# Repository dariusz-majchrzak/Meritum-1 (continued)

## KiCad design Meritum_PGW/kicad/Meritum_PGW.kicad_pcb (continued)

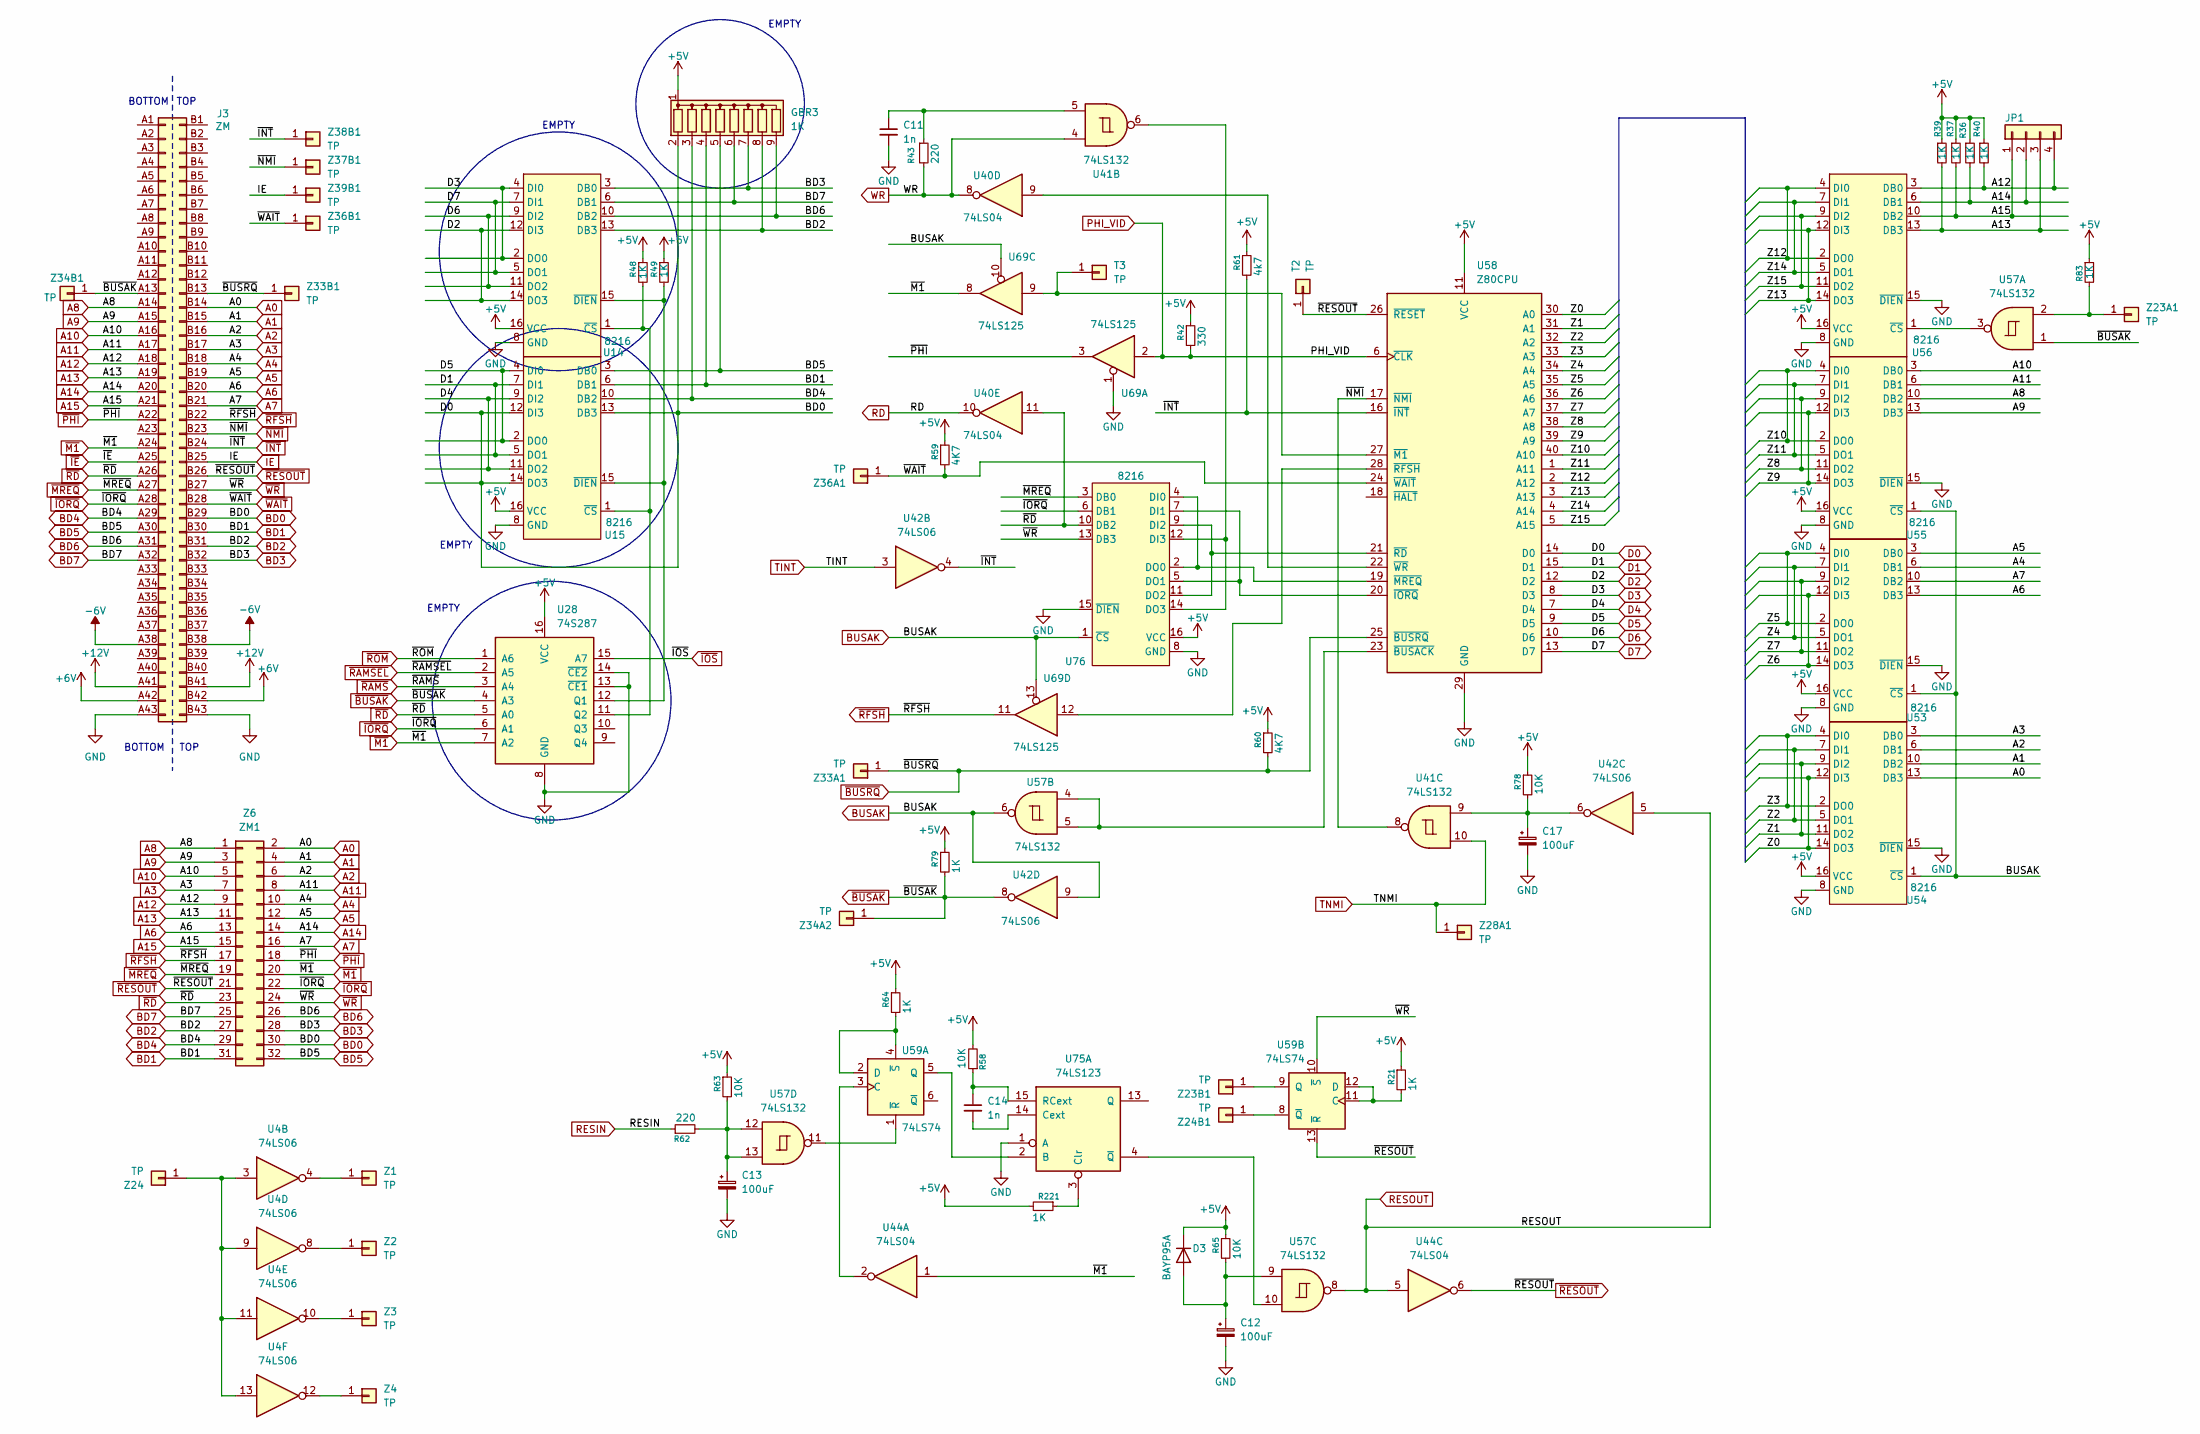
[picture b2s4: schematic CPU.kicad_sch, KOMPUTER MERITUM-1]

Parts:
C11, C14: 1n; c_200
C12, C13, C17: 100uF; CP_Radial_D5.0mm_P2.50mm
D3: BAYP95A; D_DO-35_SOD27_P10.16mm_Horizontal
GBR3: 1K; R_Array_SIP9
J3: ZM; Meritum_ZM
JP1: Conn_01x04; PinHeader_1x04_P2.54mm_Vertical
R21, R36, R37, R39, R40, R48, R49, R64, R79, R83, R221: 1K; r_400
R42: 330; r_400
R43, R62: 220; r_400
R58, R63, R65, R78: 10K; r_400
R59, R60: 4K7; r_400
R61: 4k7; r_400
T2, T3: TP; pin
U4, U42: 74LS06; DIP-14_W7.62mm_LongPads
U14, U15, U53, U54, U55, U56, U76: 8216; DIP-16_W7.62mm_LongPads
U28: 74S287; DIP-16_W7.62mm_LongPads
U40, U44: 74LS04; DIP-14_W7.62mm_LongPads
U41, U57: 74LS132; DIP-14_W7.62mm_LongPads
U58: Z80CPU; DIP-40_W15.24mm_LongPads
U59: 74LS74; DIP-14_W7.62mm_LongPads
U69: 74LS125; DIP-14_W7.62mm_LongPads
U75: 74LS123; DIP-16_W7.62mm_LongPads
Z1, Z2, Z3, Z4, Z23A1, Z23B1, Z24, Z24B1, Z28A1, Z33A1, Z33B1, Z34A2, Z34B1, Z36A1, Z36B1, Z37B1, Z38B1, Z39B1: TP; pin
Z6: ZM1; PinSocket_2x16_P2.54mm_Vertical_Meritum

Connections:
+5V: D3.1 (K), GBR3.1 (common), R21.1, R36.1, R37.1, R39.1, R40.1, R42.1, R48.1, R49.1, R58.2, R59.1, R60.1, R61.1, R63.1, R64.1, R65.1, R78.1, R79.1, R83.1, R221.2, U14.16 (VCC), U15.16 (VCC), U28.16 (VCC), U53.16 (VCC), U54.16 (VCC), U55.16 (VCC), U56.16 (VCC), U58.11 (VCC), U76.16 (VCC); also elsewhere on the board
+6V: J3.A42 (Pin_a42), J3.B42 (Pin_b42)
+12V: J3.A41 (Pin_a41), J3.B41 (Pin_b41); also elsewhere on the board
-6V: J3.A38 (Pin_a38), J3.B38 (Pin_b38)
/CPU/Z0: U54.12 (DI3), U54.14 (DO3), U58.30 (A0)
/CPU/Z1: U54.9 (DI2), U54.11 (DO2), U58.31 (A1)
/CPU/Z2: U54.5 (DO1), U54.7 (DI1), U58.32 (A2)
/CPU/Z3: U54.2 (DO0), U54.4 (DI0), U58.33 (A3)
/CPU/Z4: U53.5 (DO1), U53.7 (DI1), U58.34 (A4)
/CPU/Z5: U53.2 (DO0), U53.4 (DI0), U58.35 (A5)
/CPU/Z6: U53.12 (DI3), U53.14 (DO3), U58.36 (A6)
/CPU/Z7: U53.9 (DI2), U53.11 (DO2), U58.37 (A7)
/CPU/Z8: U55.9 (DI2), U55.11 (DO2), U58.38 (A8)
/CPU/Z9: U55.12 (DI3), U55.14 (DO3), U58.39 (A9)
/CPU/Z10: U55.2 (DO0), U55.4 (DI0), U58.40 (A10)
/CPU/Z11: U55.5 (DO1), U55.7 (DI1), U58.1 (A11)
/CPU/Z12: U56.2 (DO0), U56.4 (DI0), U58.2 (A12)
/CPU/Z13: U56.12 (DI3), U56.14 (DO3), U58.3 (A13)
/CPU/Z14: U56.5 (DO1), U56.7 (DI1), U58.4 (A14)
/CPU/Z15: U56.9 (DI2), U56.11 (DO2), U58.5 (A15)
A0: J3.B14 (Pin_b14), U54.13 (DB3), Z6.2; also elsewhere on the board
A1: J3.B15 (Pin_b15), U54.10 (DB2), Z6.4; also elsewhere on the board
A2: J3.B16 (Pin_b16), U54.6 (DB1), Z6.6; also elsewhere on the board
A3: J3.B17 (Pin_b17), U54.3 (DB0), Z6.7; also elsewhere on the board
A4: J3.B18 (Pin_b18), U53.6 (DB1), Z6.10; also elsewhere on the board
A5: J3.B19 (Pin_b19), U53.3 (DB0), Z6.12; also elsewhere on the board
A6: J3.B20 (Pin_b20), U53.13 (DB3), Z6.13; also elsewhere on the board
A7: J3.B21 (Pin_b21), U53.10 (DB2), Z6.16; also elsewhere on the board
A8: J3.A14 (Pin_a14), U55.10 (DB2), Z6.1; also elsewhere on the board
A9: J3.A15 (Pin_a15), U55.13 (DB3), Z6.3; also elsewhere on the board
A10: J3.A16 (Pin_a16), U55.3 (DB0), Z6.5; also elsewhere on the board
A11: J3.A17 (Pin_a17), U55.6 (DB1), Z6.8; also elsewhere on the board
A12: J3.A18 (Pin_a18), JP1.4, R40.2, U56.3 (DB0), Z6.9; also elsewhere on the board
A13: J3.A19 (Pin_a19), JP1.3, R39.2, U56.13 (DB3), Z6.11; also elsewhere on the board
A14: J3.A20 (Pin_a20), JP1.2, R36.2, U56.6 (DB1), Z6.14; also elsewhere on the board
A15: J3.A21 (Pin_a21), JP1.1, R37.2, U56.10 (DB2), Z6.15; also elsewhere on the board
BD0: GBR3.2 (R1), J3.B29 (Pin_b29), U15.12 (DI3), U15.13 (DB3), U15.14 (DO3), U58.14 (D0), Z6.30; also elsewhere on the board
BD1: GBR3.4 (R3), J3.B30 (Pin_b30), U15.6 (DB1), Z6.31
BD2: GBR3.8 (R7), J3.B31 (Pin_b31), U14.13 (DB3), Z6.27
BD3: GBR3.7 (R6), J3.B32 (Pin_b32), U14.3 (DB0), Z6.28
BD4: GBR3.3 (R2), J3.A29 (Pin_a29), U15.10 (DB2), Z6.29
BD5: GBR3.5 (R4), J3.A30 (Pin_a30), U15.3 (DB0), Z6.32
BD6: GBR3.9 (R8), J3.A31 (Pin_a31), U14.10 (DB2), Z6.26
BD7: GBR3.6 (R5), J3.A32 (Pin_a32), U14.6 (DB1), Z6.25
BUSAK: U42.9, U53.1 (~CS), U54.1 (~CS), U55.1 (~CS), U57.6, U69.10, U69.13, U76.1 (~CS)
D1: U15.5 (DO1), U15.7 (DI1), U58.15 (D1); also elsewhere on the board
D2: U14.12 (DI3), U14.14 (DO3), U58.12 (D2); also elsewhere on the board
D3: U14.2 (DO0), U14.4 (DI0), U58.8 (D3); also elsewhere on the board
D4: U15.9 (DI2), U15.11 (DO2), U58.7 (D4); also elsewhere on the board
D5: U15.2 (DO0), U15.4 (DI0), U58.9 (D5); also elsewhere on the board
D6: U14.9 (DI2), U14.11 (DO2), U58.10 (D6); also elsewhere on the board
D7: U14.5 (DO1), U14.7 (DI1), U58.13 (D7); also elsewhere on the board
GND: C11.2, C12.2, C13.2, C17.2, J3.A43 (Pin_a43), J3.B43 (Pin_b43), U14.8 (GND), U15.8 (GND), U28.8 (GND), U28.13 (~CE1), U28.14 (~CE2), U53.8 (GND), U53.15 (~DIEN), U54.8 (GND), U54.15 (~DIEN), U55.8 (GND), U55.15 (~DIEN), U56.8 (GND), U56.15 (~DIEN), U58.29 (GND), U69.1, U75.1 (A), U76.8 (GND), U76.15 (~DIEN); also elsewhere on the board
IE: J3.B25 (Pin_b25), Z39B1.1 (Pin_1_1)
unnamed: C11.1, R43.1, U41.5
unnamed: C13.1, R62.2, R63.2, U57.12, U57.13
unnamed: C17.1, R78.2, U41.9, U42.6
unnamed: C12.1, D3.2 (A), R65.2, U57.9
unnamed: T3.1 (Pin_1_1), U58.27 (~M1), U69.9
unnamed: R48.2, U14.1 (~CS), U15.1 (~CS), U28.11 (Q2)
unnamed: R49.2, U14.15 (~DIEN), U15.15 (~DIEN), U28.12 (Q1)
unnamed: U56.1 (~CS), U57.3
unnamed: U57.4, U57.5, U58.23 (~BUSACK)
unnamed: U58.20 (~IORQ), U76.5 (DO1), U76.7 (DI1)
unnamed: U58.19 (~MREQ), U76.2 (DO0), U76.4 (DI0)
unnamed: U58.21 (~RD), U76.9 (DI2), U76.11 (DO2)
unnamed: U58.28 (~RFSH), U69.12
unnamed: U40.9, U58.22 (~WR)
unnamed: U44.2, U59.3 (C)
unnamed: R64.2, U59.2 (D), U59.4 (~S)
unnamed: U59.5 (Q), U75.2 (B)
unnamed: U57.11, U59.1 (~R)
unnamed: R21.2, U59.11 (C), U59.12 (D)
unnamed: U59.9 (Q), Z23B1.1 (Pin_1_1)
unnamed: U59.8 (~Q), Z24B1.1 (Pin_1_1)
unnamed: C14.2, U75.14 (Cext)
unnamed: R221.1, U75.3 (Clr)
unnamed: C14.1, R58.1, U75.15 (RCext)
unnamed: U57.10, U75.4 (~Q)
unnamed: U41.6, U76.12 (DI3), U76.14 (DO3)
unnamed: U4.4, Z1.1 (Pin_1_1)
unnamed: U4.8, Z2.1 (Pin_1_1)
unnamed: U4.10, Z3.1 (Pin_1_1)
unnamed: U4.12, Z4.1 (Pin_1_1)
unnamed: R83.2, U57.2, Z23A1.1 (Pin_1_1)
unnamed: U4.3, U4.9, U4.11, U4.13, Z24.1 (Pin_1_1)
PHI_VID: R42.2, U58.6 (~CLK), U69.2; also elsewhere on the board
RD: U40.10; also elsewhere on the board
RESIN: R62.1; also elsewhere on the board
RESOUT: U42.5, U44.5, U57.8; also elsewhere on the board
TINT: U42.3; also elsewhere on the board
TNMI: U41.10, Z28A1.1 (Pin_1_1); also elsewhere on the board
WR: R43.2, U40.8, U41.4; also elsewhere on the board
~BUSAK: J3.A13 (Pin_a13), R79.2, U28.4 (A3), U42.8, U57.1, Z34A2.1 (Pin_1_1), Z34B1.1 (Pin_1_1)
~BUSRQ: J3.B13 (Pin_b13), R60.2, U58.25 (~BUSRQ), Z33A1.1 (Pin_1_1), Z33B1.1 (Pin_1_1)
~IE: J3.A25 (Pin_a25)
~INT: J3.B24 (Pin_b24), R61.2, U42.4, U58.16 (~INT), Z38B1.1 (Pin_1_1)
~IORQ: J3.A28 (Pin_a28), U28.6 (A1), U76.6 (DB1), Z6.22; also elsewhere on the board
~IOS: U28.15 (A7); also elsewhere on the board
~M1: J3.A24 (Pin_a24), U28.7 (A2), U44.1, U69.8, Z6.20
~MREQ: J3.A27 (Pin_a27), U76.3 (DB0), Z6.19; also elsewhere on the board
~NMI: J3.B23 (Pin_b23), U41.8, U58.17 (~NMI), Z37B1.1 (Pin_1_1)
~PHI: J3.A22 (Pin_a22), U69.3, Z6.18; also elsewhere on the board
~RAMSEL: U28.2 (A5); also elsewhere on the board
~RAMS: U28.3 (A4); also elsewhere on the board
~RD: J3.A26 (Pin_a26), U28.5 (A0), U40.11, U76.10 (DB2), Z6.23; also elsewhere on the board
~RESOUT: J3.B26 (Pin_b26), T2.1 (Pin_1_1), U44.6, U58.26 (~RESET), U59.13 (~R), Z6.21
~RFSH: J3.B22 (Pin_b22), U69.11, Z6.17; also elsewhere on the board
~ROM: U28.1 (A6); also elsewhere on the board
~WAIT: J3.B28 (Pin_b28), R59.2, U58.24 (~WAIT), Z36A1.1 (Pin_1_1), Z36B1.1 (Pin_1_1)
~WR: J3.B27 (Pin_b27), U59.10 (~S), U76.13 (DB3), Z6.24; also elsewhere on the board

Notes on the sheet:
TOP
EMPTY
BOTTOM

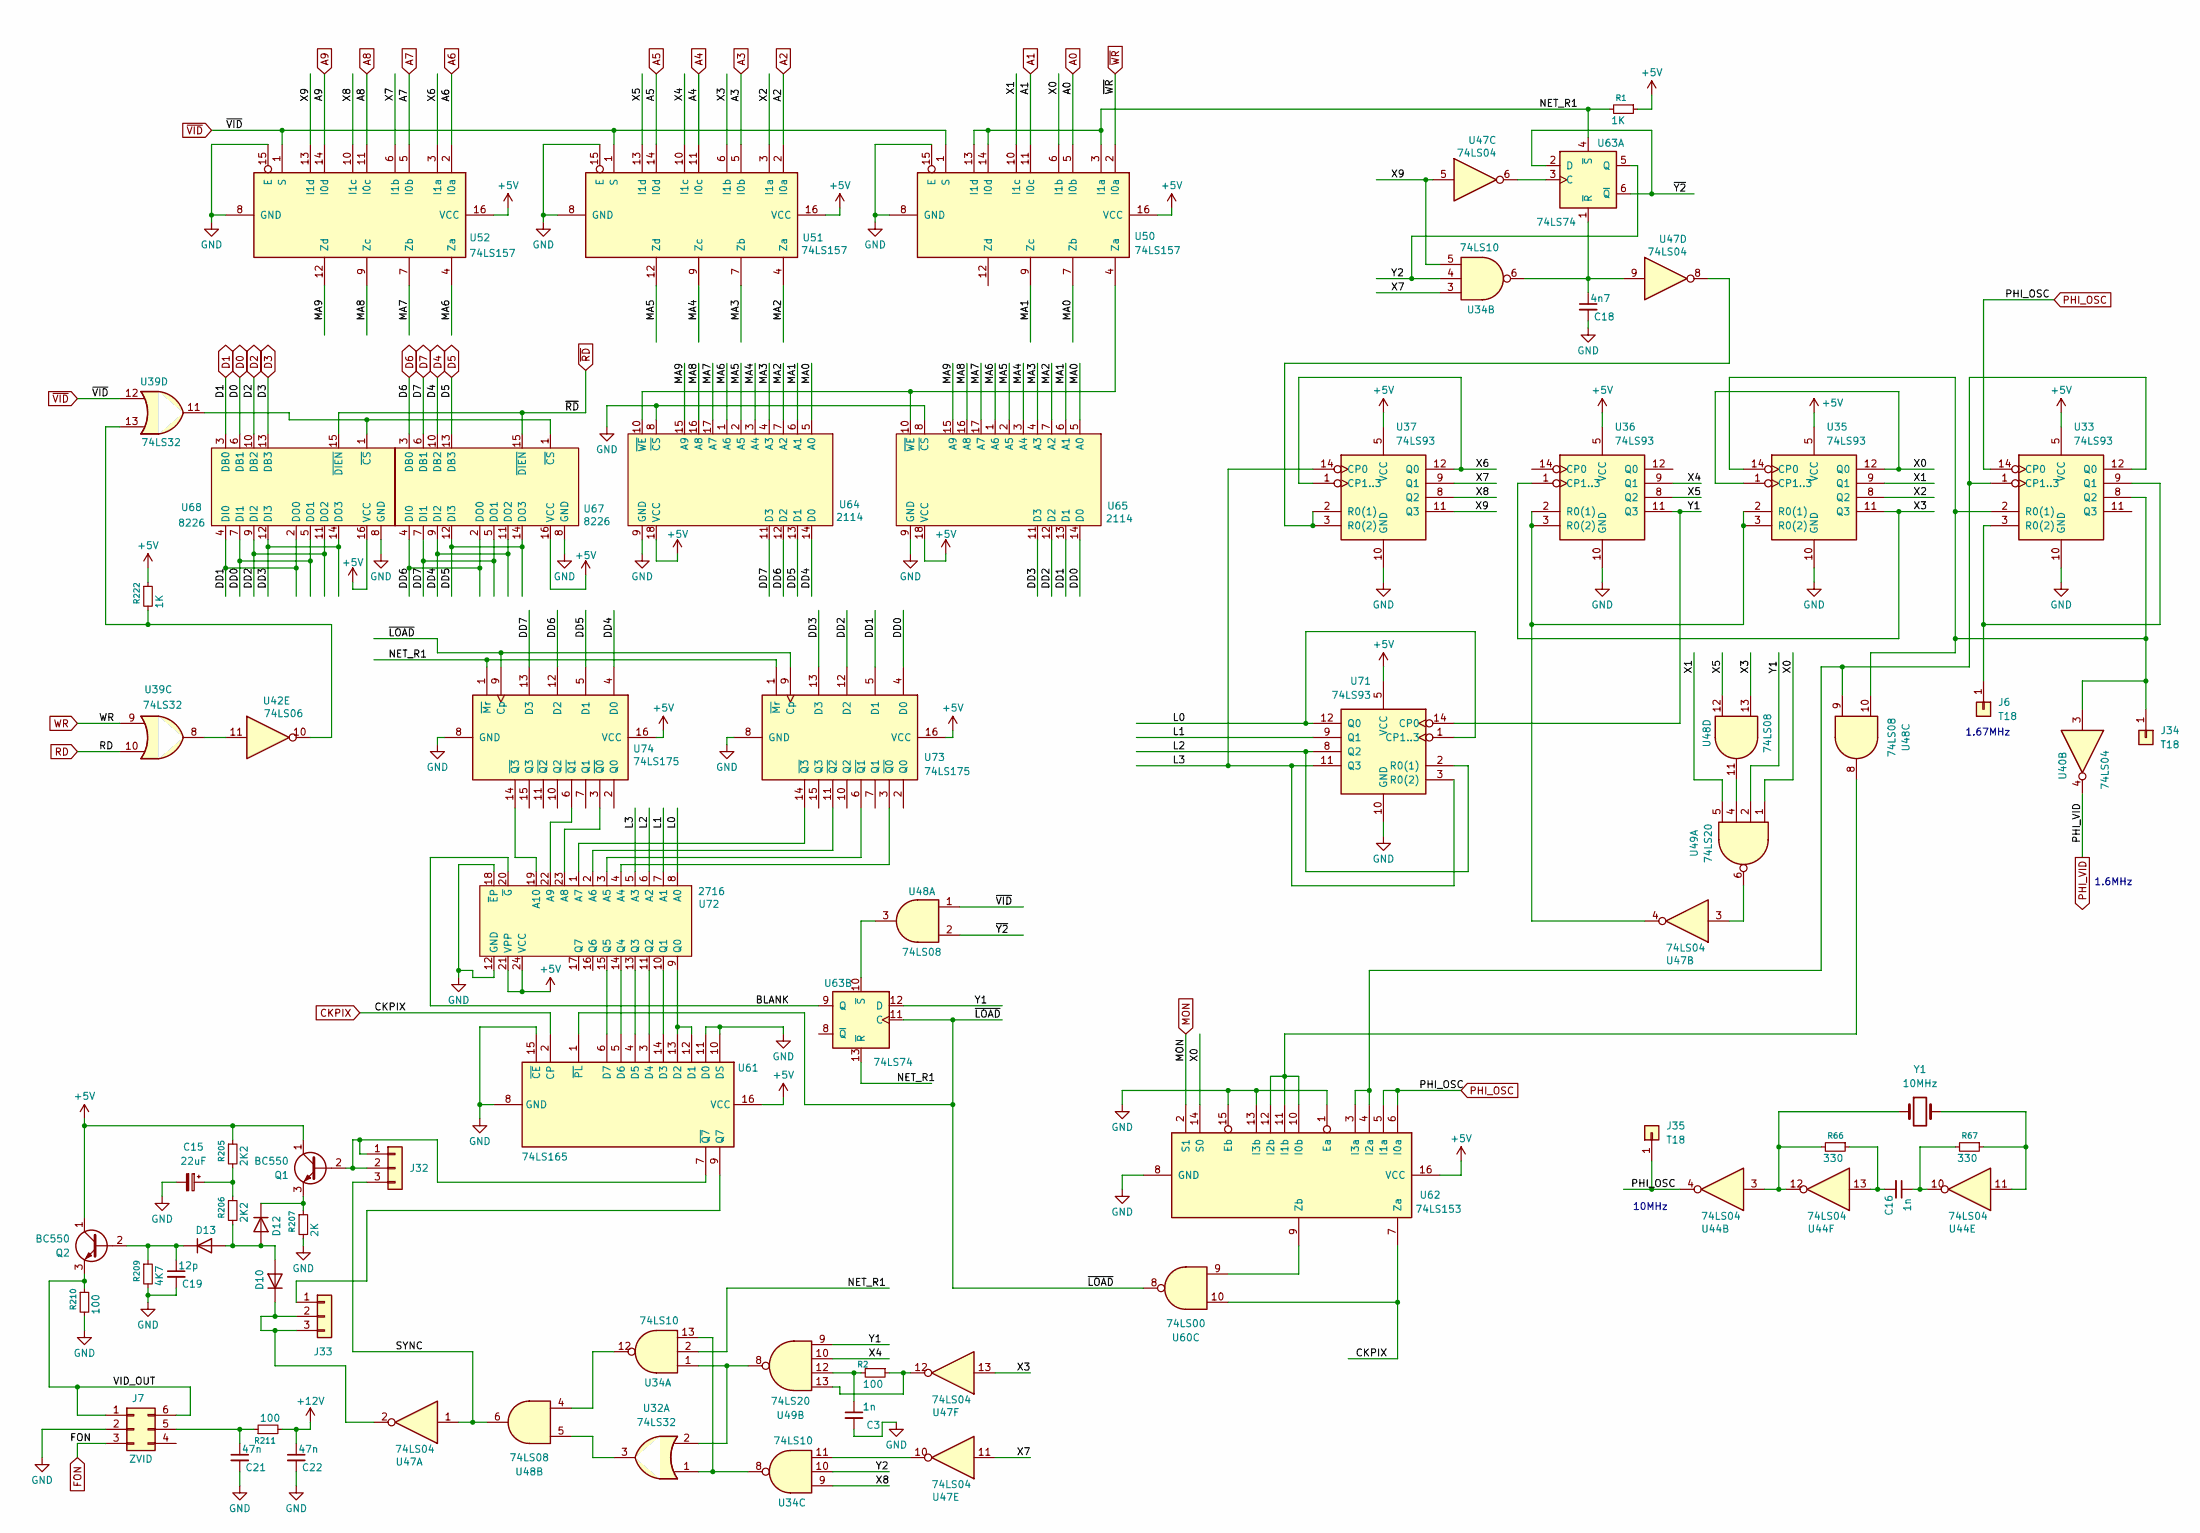
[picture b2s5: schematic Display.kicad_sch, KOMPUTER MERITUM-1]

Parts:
C3, C16: 1n; c_200
C15: 22uF; CP_Radial_D5.0mm_P2.50mm
C18: 4n7; c_100
C19: 12p; C_Rect_L7.0mm_W2.0mm_P5.00mm
C21, C22: 47n; c_200
D10, D12, D13: 1N4148WT; D_DO-35_SOD27_P10.16mm_Horizontal
J6, J34, J35: T18; pin
J7: ZVID; PinHeader_2x03_P2.54mm_Vertical
J32, J33: Conn_01x03; PinHeader_1x03_P2.54mm_Vertical
Q1, Q2: BC550; TO-92L
R1, R222: 1K; r_400
R2: 100; R_Axial_DIN0207_L6.3mm_D2.5mm_P7.62mm_Horizontal
R66, R67: 330; r_400
R205: 2K2; r_400
R206: 2K2; R_Axial_DIN0207_L6.3mm_D2.5mm_P2.54mm_Vertical
R207: 2K; r_400
R209: 4K7; r_400
R210, R211: 100; r_400
U32, U39: 74LS32; DIP-14_W7.62mm_LongPads
U33, U35, U36, U37, U71: 74LS93; DIP-14_W7.62mm_LongPads
U34: 74LS10; DIP-14_W7.62mm_LongPads
U40, U44, U47: 74LS04; DIP-14_W7.62mm_LongPads
U42: 74LS06; DIP-14_W7.62mm_LongPads
U48: 74LS08; DIP-14_W7.62mm_LongPads
U49: 74LS20; DIP-14_W7.62mm_LongPads
U50, U51, U52: 74LS157; DIP-16_W7.62mm_LongPads
U60: 74LS00; DIP-14_W7.62mm_LongPads
U61: 74LS165; DIP-16_W7.62mm_LongPads
U62: 74LS153; DIP-16_W7.62mm_LongPads
U63: 74LS74; DIP-14_W7.62mm_LongPads
U64, U65: 2114; DIP-18_W7.62mm_Socket_LongPads
U67, U68: 8226; DIP-16_W7.62mm_LongPads
U72: 2716; DIP-24_W15.24mm_LongPads
U73, U74: 74LS175; DIP-16_W7.62mm_LongPads
Y1: 10MHz; Crystal_HC49-4H_Vertical

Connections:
+5V: Q1.1 (C), Q2.1 (C), R1.1, R205.1, R222.1, U33.5 (VCC), U35.5 (VCC), U36.5 (VCC), U37.5 (VCC), U50.16 (VCC), U51.16 (VCC), U52.16 (VCC), U61.16 (VCC), U62.16 (VCC), U64.18 (VCC), U65.18 (VCC), U67.16 (VCC), U68.16 (VCC), U71.5 (VCC), U72.21 (VPP), U72.24 (VCC), U73.16 (VCC), U74.16 (VCC); also elsewhere on the board
+12V: C22.1, R211.2; also elsewhere on the board
/Display/BLANK: U63.9 (Q), U72.20 (~G)
/Display/DD0: U65.14 (D0), U68.5 (DO1), U68.7 (DI1), U73.4 (D0)
/Display/DD1: U65.13 (D1), U68.2 (DO0), U68.4 (DI0), U73.5 (D1)
/Display/DD2: U65.12 (D2), U68.9 (DI2), U68.11 (DO2), U73.12 (D2)
/Display/DD3: U65.11 (D3), U68.12 (DI3), U68.14 (DO3), U73.13 (D3)
/Display/DD4: U64.14 (D0), U67.9 (DI2), U67.11 (DO2), U74.4 (D0)
/Display/DD5: U64.13 (D1), U67.12 (DI3), U67.14 (DO3), U74.5 (D1)
/Display/DD6: U64.12 (D2), U67.2 (DO0), U67.4 (DI0), U74.12 (D2)
/Display/DD7: U64.11 (D3), U67.5 (DO1), U67.7 (DI1), U74.13 (D3)
/Display/L0: U71.1 (CP1..3), U71.12 (Q0), U72.8 (A0)
/Display/L1: U71.9 (Q1), U72.7 (A1)
/Display/L2: U71.2 (R0(1)), U71.8 (Q2), U72.6 (A2)
/Display/L3: U37.14 (CP0), U71.3 (R0(2)), U71.11 (Q3), U72.5 (A3)
/Display/MA0: U50.7 (Zb), U64.5 (A0), U65.5 (A0)
/Display/MA1: U50.9 (Zc), U64.6 (A1), U65.6 (A1)
/Display/MA2: U51.4 (Za), U64.7 (A2), U65.7 (A2)
/Display/MA3: U51.7 (Zb), U64.4 (A3), U65.4 (A3)
/Display/MA4: U51.9 (Zc), U64.3 (A4), U65.3 (A4)
/Display/MA5: U51.12 (Zd), U64.2 (A5), U65.2 (A5)
/Display/MA6: U52.4 (Za), U64.1 (A6), U65.1 (A6)
/Display/MA7: U52.7 (Zb), U64.17 (A7), U65.17 (A7)
/Display/MA8: U52.9 (Zc), U64.16 (A8), U65.16 (A8)
/Display/MA9: U52.12 (Zd), U64.15 (A9), U65.15 (A9)
/Display/NET_R1: R1.2, U34.2, U50.3 (I1a), U50.13 (I1d), U50.14 (I0d), U63.4 (~S), U63.13 (~R), U73.1 (~Mr), U74.1 (~Mr)
/Display/SYNC: J32.3, U47.1, U48.6
/Display/VID_OUT: J7.1, J7.6, Q2.3 (E), R210.1
/Display/X0: U35.1 (CP1..3), U35.12 (Q0), U49.1, U50.6 (I1b), U62.14 (S0)
/Display/X1: U35.9 (Q1), U49.5, U50.10 (I1c)
/Display/X2: U35.8 (Q2), U51.3 (I1a)
/Display/X3: U35.11 (Q3), U36.1 (CP1..3), U47.13, U48.13, U51.6 (I1b)
/Display/X4: U36.9 (Q1), U49.10, U51.10 (I1c)
/Display/X5: U36.8 (Q2), U48.12, U51.13 (I1d)
/Display/X6: U37.1 (CP1..3), U37.12 (Q0), U52.3 (I1a)
/Display/X7: U34.3, U37.9 (Q1), U47.11, U52.6 (I1b)
/Display/X8: U34.9, U37.8 (Q2), U52.10 (I1c)
/Display/X9: U34.5, U37.11 (Q3), U47.5, U52.13 (I1d)
/Display/Y1: U36.11 (Q3), U49.2, U49.9, U63.12 (D), U71.14 (CP0)
/Display/Y2: U34.4, U34.10, U63.5 (Q)
/Display/~LOAD: U60.8, U61.1 (~PL), U63.11 (C), U73.9 (Cp), U74.9 (Cp)
/Display/~Y2: U48.2, U63.2 (D), U63.6 (~Q)
A0: U50.5 (I0b); also elsewhere on the board
A1: U50.11 (I0c); also elsewhere on the board
A2: U51.2 (I0a); also elsewhere on the board
A3: U51.5 (I0b); also elsewhere on the board
A4: U51.11 (I0c); also elsewhere on the board
A5: U51.14 (I0d); also elsewhere on the board
A6: U52.2 (I0a); also elsewhere on the board
A7: U52.5 (I0b); also elsewhere on the board
A8: U52.11 (I0c); also elsewhere on the board
A9: U52.14 (I0d); also elsewhere on the board
BD0: U68.6 (DB1); also elsewhere on the board
CKPIX: U60.10, U61.2 (CP), U62.7 (Za)
D1: U68.3 (DB0); also elsewhere on the board
D2: U68.10 (DB2); also elsewhere on the board
D3: U68.13 (DB3); also elsewhere on the board
D4: U67.10 (DB2); also elsewhere on the board
D5: U67.13 (DB3); also elsewhere on the board
D6: U67.3 (DB0); also elsewhere on the board
D7: U67.6 (DB1); also elsewhere on the board
FON: J7.3; also elsewhere on the board
GND: C3.2, C15.2, C18.2, C19.2, C21.2, C22.2, J7.2, R207.2, R209.2, R210.2, U33.10 (GND), U35.10 (GND), U36.10 (GND), U37.10 (GND), U50.8 (GND), U50.15 (E), U51.8 (GND), U51.15 (E), U52.8 (GND), U52.15 (E), U61.8 (GND), U61.10 (DS), U61.11 (D0), U61.15 (~CE), U62.1 (Ea), U62.8 (GND), U62.13 (I3b), U62.15 (Eb), U64.8 (~CS), U64.9 (GND), U65.8 (~CS), U65.9 (GND), U67.8 (GND), U68.8 (GND), U71.10 (GND), U72.12 (GND), U72.18 (~EP), U73.8 (GND), U74.8 (GND); also elsewhere on the board
MON: U62.2 (S1); also elsewhere on the board
unnamed: C3.1, R2.2, U49.12
unnamed: C15.1, R205.2, R206.1
unnamed: C16.1, R67.2, U44.10
unnamed: C16.2, R66.1, U44.13
unnamed: D10.2 (A), D12.2 (A), D13.2 (A), R206.2
unnamed: D10.1 (K), J33.2, J33.3, U47.2
unnamed: D12.1 (K), Q1.3 (E), R207.1
unnamed: C19.1, D13.1 (K), Q2.2 (B), R209.1
unnamed: J6.1 (Pin_1_1), U33.3 (R0(2)), U33.9 (Q1)
unnamed: C21.1, J7.5, R211.1
unnamed: J32.1, J32.2, Q1.2 (B), U61.7 (~Q7)
unnamed: J33.1, U61.9 (Q7)
unnamed: J34.1 (Pin_1_1), U33.2 (R0(1)), U33.8 (Q2), U35.14 (CP0), U40.3, U48.10
unnamed: R2.1, U47.12, U49.13
unnamed: R66.2, U44.3, U44.12, Y1.1
unnamed: R67.1, U44.11, Y1.2
unnamed: R222.2, U39.13, U42.10
unnamed: U32.1, U34.8, U34.13
unnamed: U32.2, U34.1, U49.8
unnamed: U32.3, U48.5
unnamed: U33.1 (CP1..3), U33.12 (Q0), U48.9, U62.3 (I3a), U62.4 (I2a)
unnamed: U34.11, U47.10
unnamed: U34.12, U48.4
unnamed: U35.2 (R0(1)), U35.3 (R0(2)), U36.2 (R0(1)), U36.3 (R0(2)), U47.4
unnamed: U37.2 (R0(1)), U37.3 (R0(2)), U47.8
unnamed: U39.8, U42.11
unnamed: U47.3, U49.6
unnamed: U48.11, U49.4
unnamed: U50.4 (Za), U64.10 (~WE), U65.10 (~WE)
unnamed: U61.12 (D1), U61.13 (D2), U72.9 (Q0)
unnamed: U61.14 (D3), U72.10 (Q1)
unnamed: U61.3 (D4), U72.11 (Q2)
unnamed: U61.4 (D5), U72.13 (Q3)
unnamed: U61.5 (D6), U72.14 (Q4)
unnamed: U61.6 (D7), U72.15 (Q5)
unnamed: U48.8, U62.10 (I0b), U62.11 (I1b), U62.12 (I2b)
unnamed: U60.9, U62.9 (Zb)
unnamed: U47.6, U63.3 (C)
unnamed: C18.1, U34.6, U47.9, U63.1 (~R)
unnamed: U48.3, U63.10 (~S)
unnamed: U39.11, U67.1 (~CS), U68.1 (~CS)
unnamed: U72.4 (A4), U73.3 (~Q0)
unnamed: U72.3 (A5), U73.6 (~Q1)
unnamed: U72.2 (A6), U73.11 (~Q2)
unnamed: U72.1 (A7), U73.14 (~Q3)
unnamed: U72.23 (A8), U74.3 (~Q0)
unnamed: U72.22 (A9), U74.6 (~Q1)
unnamed: U72.19 (A10), U74.14 (~Q3)
PHI_OSC: J35.1 (Pin_1_1), U33.14 (CP0), U44.4, U62.5 (I1a), U62.6 (I0a); also elsewhere on the board
PHI_VID: U40.4; also elsewhere on the board
RD: U39.10; also elsewhere on the board
WR: U39.9; also elsewhere on the board
~RD: U67.15 (~DIEN), U68.15 (~DIEN); also elsewhere on the board
~VID: U39.12, U48.1, U50.1 (S), U51.1 (S), U52.1 (S); also elsewhere on the board
~WR: U50.2 (I0a); also elsewhere on the board

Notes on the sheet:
1.6MHz
10MHz
1.67MHz

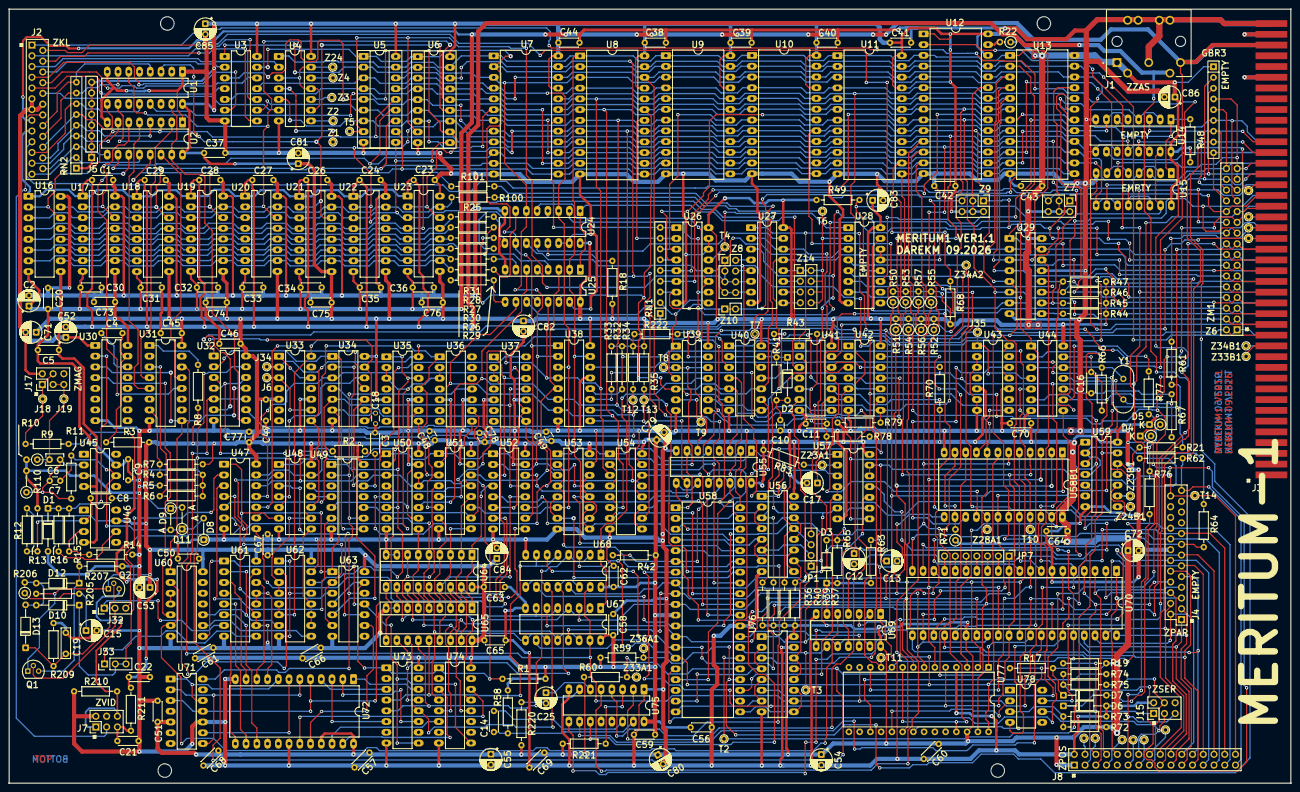
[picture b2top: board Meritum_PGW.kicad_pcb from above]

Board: 4 copper layers, 303.0 x 183.0 mm, 331 parts (0 on the bottom side), 337 nets.
